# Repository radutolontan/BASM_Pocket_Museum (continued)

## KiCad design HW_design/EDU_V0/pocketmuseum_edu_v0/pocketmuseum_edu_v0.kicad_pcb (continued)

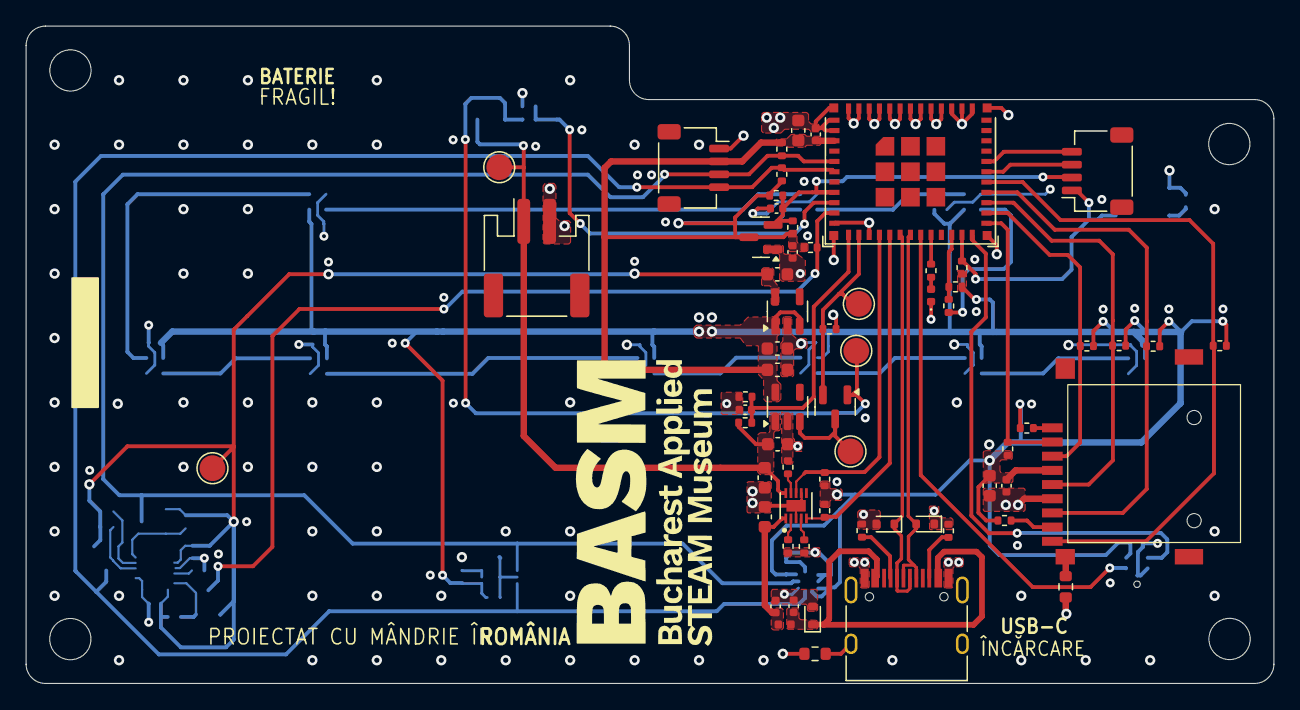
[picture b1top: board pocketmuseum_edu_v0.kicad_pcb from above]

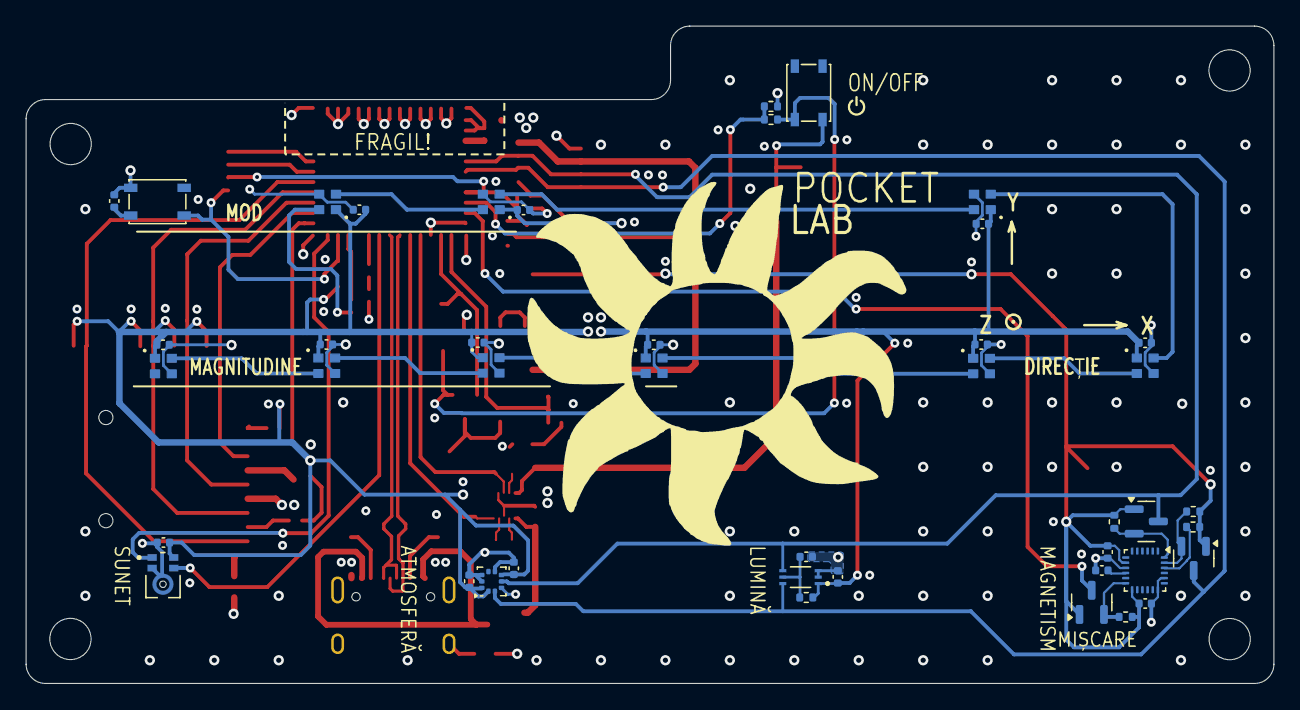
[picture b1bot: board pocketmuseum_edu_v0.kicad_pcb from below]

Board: 4 copper layers, 96.8 x 51.0 mm, 111 parts (43 on the bottom side), 56 nets.

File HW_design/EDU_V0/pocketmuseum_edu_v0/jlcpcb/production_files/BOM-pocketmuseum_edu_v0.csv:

Comment,Designator,Footprint,LCSC,Quantity
TF-015,J201,TF-015_SOFNG,C113206,1
1k,R308,R_0402_1005Metric,C11702,1
1u,"C101,C102,C105,C204,C301,C307,C401,C402,C403,C404,C405,C406,C407,C408,C409",C_0402_1005Metric,C14445,15
0u1,"C106,C202,C203,C207,C302,C303,C304,C305,C306,C308",C_0402_1005Metric,C1525,10
SM04B-SRSS-TB,"J205,J206",JST_SH_SM04B-SRSS-TB_1x04-1MP_P1.00mm_Horizontal,C160404,2
USB_C_Receptacle_USB2.0_16P,J101,USB_C_Receptacle_HRO_TYPE-C-31-M-12,C165948,1
10u,"C103,C104,C107,C108,C109,C110,C201,C206",C_0603_1608Metric,C1691,8
AP2112K-1.8,U104,SOT-23-5,C176944,1
BAT54C,D104,SOT-23,C181200,1
0R,"R114,R208",R_0603_1608Metric,C21189,2
LED,D208,LED_0402_1005Metric,C21260817,1
PTS810SJG250,"SW101,SW201",SW_SPST_PTS810,C221895,2
470R,R203,R_0402_1005Metric,C25117,1
100k,R110,R_0402_1005Metric,C25741,1
10k,"R105,R106,R107,R112,R113,R204,R205,R206,R207,R209,R210,R211,R212,R213,R214,R305",R_0402_1005Metric,C25744,16
1k2,"R103,R215",R_0402_1005Metric,C25862,2
3k3,R111,R_0402_1005Metric,C25890,1
5k1,"R101,R102,R201,R202,R301,R302,R303,R304",R_0402_1005Metric,C25905,8
6k8,R104,R_0402_1005Metric,C25917,1
178k,R109,R_0402_1005Metric,C26995,1
SK6805-EC20,"D401,D402,D403,D404,D405,D406,D407,D408,D409",SK68xx-EC20,C2890036,9
JST PH S2B,J102,JST_PH_S2B-PH-SM4-TB_1x02-1MP_P2.00mm_Horizontal,C295747,1
T3902,U304,MMIC,C3171752,1
61k9,R108,R_0402_1005Metric,C327331,1
APX803-29SAG,U102,SOT-23,C460551,1
AP2112K-3.3,U103,SOT-23-5,C51118,1
LESD5D5.0CT1G,"D101,D102,D103",D_SOD-523,C5199850,3
ICP20100,U302,ST_HLGA-10_2x2mm_P0.5mm_LayoutBorder3x2y,C5343527,1
ESP32-C6-MINI-1/U,U201,ESP32-C6-MINI-1,C5736265,1
ICM-20948,U301,InvenSense_QFN-24_3x3mm_P0.4mm,C726001,1
10n,L101,L_0402_1005Metric,C77103,1
BH1750FVI,U303,XDCR_BH1750FVI-TR,C78960,1
BQ24040,U101,QFN_10_BQ24040,C81080,1
BSS138,"Q301,Q302,Q303",SOT-23,C8490,3
TestPoint,TP105,TestPoint_Pad_D2.0mm,,1
TestPoint,TP101,TestPoint_Pad_D2.0mm,,1
TestPoint,TP104,TestPoint_Pad_D2.0mm,,1
TestPoint,TP102,TestPoint_Pad_D2.0mm,,1
TestPoint,TP103,TestPoint_Pad_D2.0mm,,1

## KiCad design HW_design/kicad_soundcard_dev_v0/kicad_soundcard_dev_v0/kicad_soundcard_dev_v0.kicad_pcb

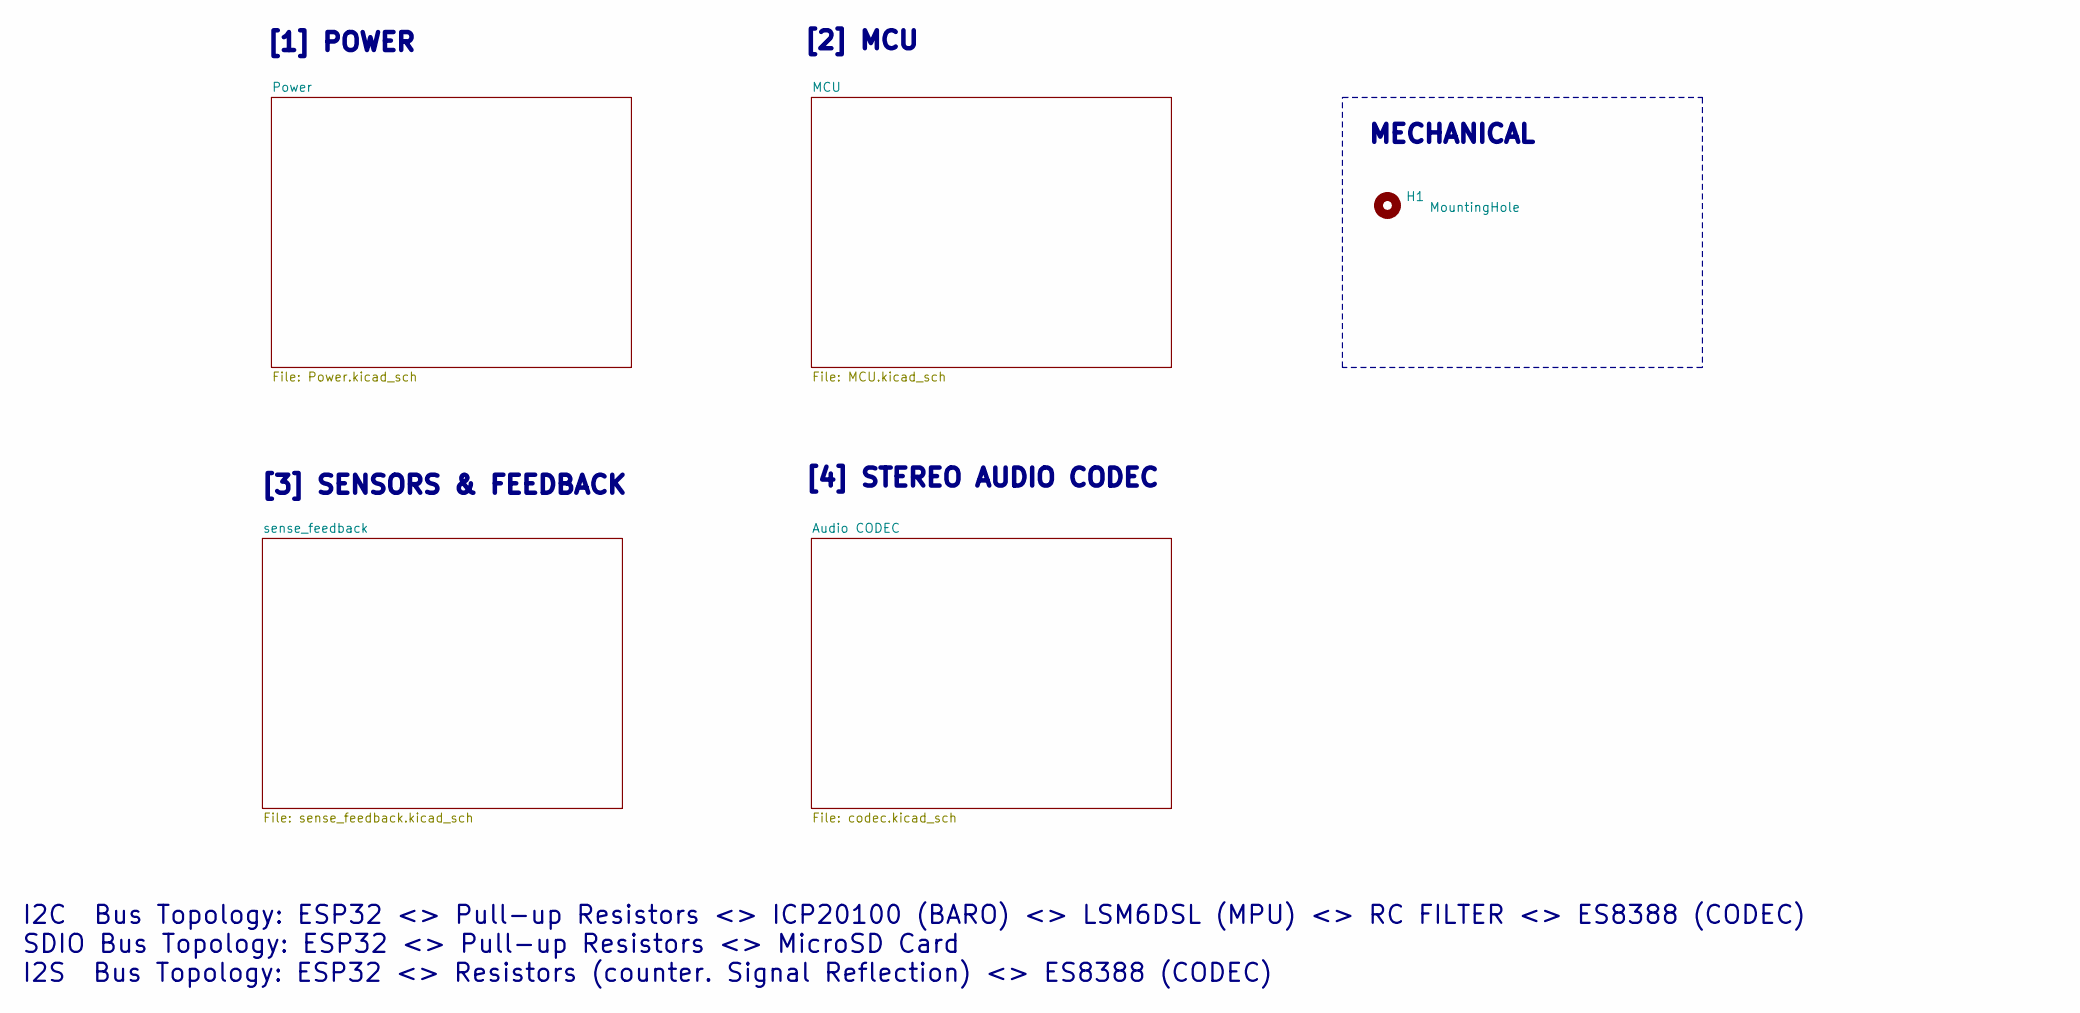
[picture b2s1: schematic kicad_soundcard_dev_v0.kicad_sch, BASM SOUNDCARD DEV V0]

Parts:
H1: MountingHole; MountingHole_3.5mm

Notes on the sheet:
[4] STEREO AUDIO CODEC
[1] POWER
I2C Bus Topology: ESP32 <> Pull-up Resistors <> ICP20100 (BARO) <> LSM6DSL (MPU) <> RC FILTER <> ES8388 (CODEC) SDIO Bus Topology: ESP32 <> Pull-up Resistors <> MicroSD Card I2S Bus Topology: ESP32 <> Resistors (counter. Signal Reflection) <> ES8388 (CODEC)
[2] MCU
[3] SENSORS & FEEDBACK
MECHANICAL

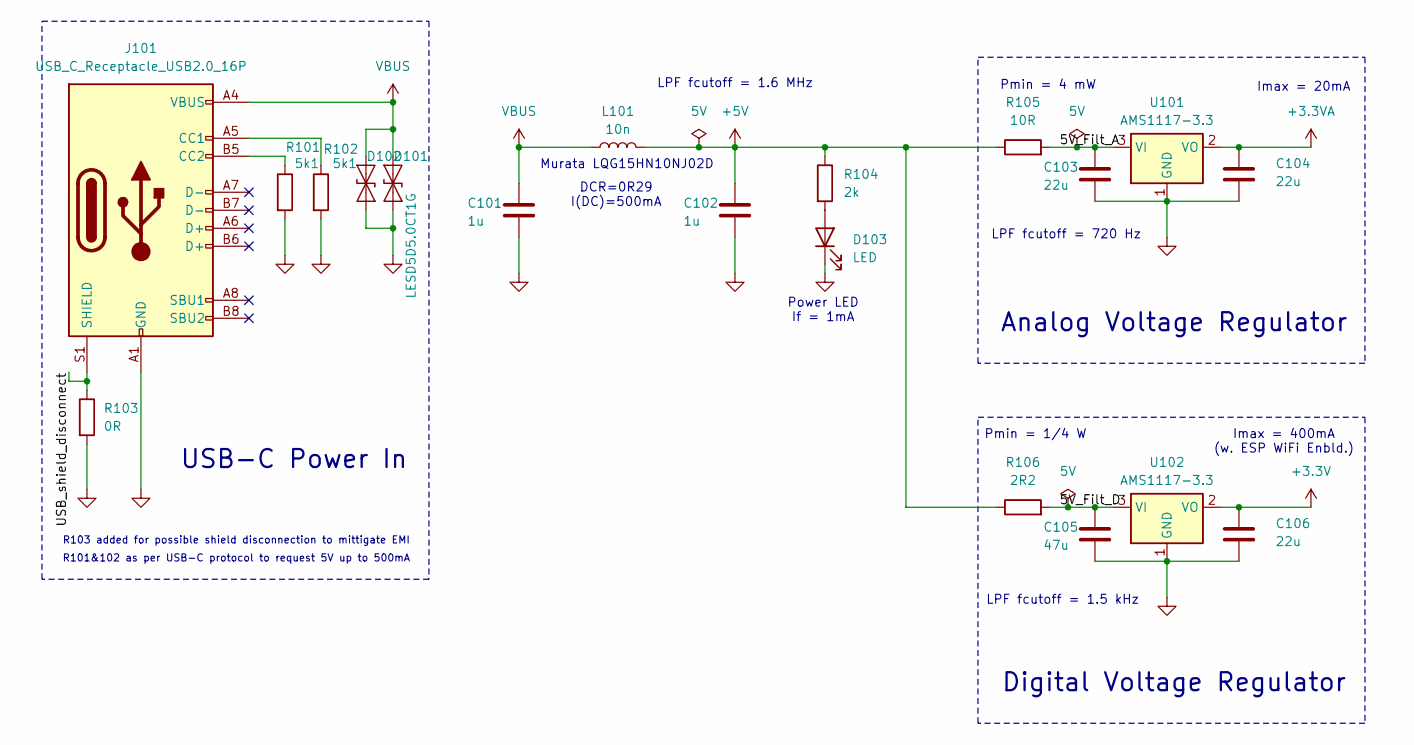
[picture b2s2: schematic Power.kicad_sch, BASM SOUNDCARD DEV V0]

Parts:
C101, C102: 1u; C_0402_1005Metric
C103, C104, C106: 22u; C_0603_1608Metric
C105: 47u; C_0603_1608Metric
D101, D102: LESD5D5.0CT1G; D_SOD-523
D103: LED; LED_0402_1005Metric
J101: USB_C_Receptacle_USB2.0_16P; USB_C_Receptacle_HRO_TYPE-C-31-M-12
L101: 10n; L_0402_1005Metric
R101, R102: 5k1; R_0402_1005Metric
R103: 0R; R_0603_1608Metric
R104: 2k; R_0402_1005Metric
R105: 10R; R_0603_1608Metric
R106: 2R2; R_1206_3216Metric
U101, U102: AMS1117-3.3; SOT-223-3_TabPin2

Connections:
+3.3V: C106.1, U102.2 (VO); also elsewhere on the board
+3.3VA: C104.1, U101.2 (VO); also elsewhere on the board
+5V: C102.1, L101.2, R104.1, R105.1, R106.1
/Power/5V_Filt_A: C103.1, R105.2, U101.3 (VI)
/Power/5V_Filt_D: C105.1, R106.2, U102.3 (VI)
/Power/USB_shield_disconnect: J101.S1 (SHIELD), R103.1
GND: C101.2, C102.2, C103.2, C104.2, C105.2, C106.2, D101.1 (A1), D102.1 (A1), D103.1 (K), J101.A1 (GND), J101.A12 (GND), J101.B1 (GND), J101.B12 (GND), R101.2, R102.2, R103.2, U101.1 (GND), U102.1 (GND); also elsewhere on the board
unnamed: D103.2 (A), R104.2
unnamed: J101.A5 (CC1), R102.1
unnamed: J101.B5 (CC2), R101.1
VBUS: C101.1, D101.2 (A2), D102.2 (A2), J101.A4 (VBUS), J101.A9 (VBUS), J101.B4 (VBUS), J101.B9 (VBUS), L101.1; also elsewhere on the board

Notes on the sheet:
Analog Voltage Regulator
Murata LQG15HN10NJ02D
Imax = 20mA
Pmin = 1/4 W
LPF fcutoff = 1.5 kHz
Pmin = 4 mW
DCR=0R29 I(DC)=500mA
USB-C Power In
Imax = 400mA (w. ESP WiFi Enbld.)
Power LED If = 1mA
Digital Voltage Regulator
LPF fcutoff = 1.6 MHz
R103 added for possible shield disconnection to mittigate EMI
R101&102 as per USB-C protocol to request 5V up to 500mA
LPF fcutoff = 720 Hz

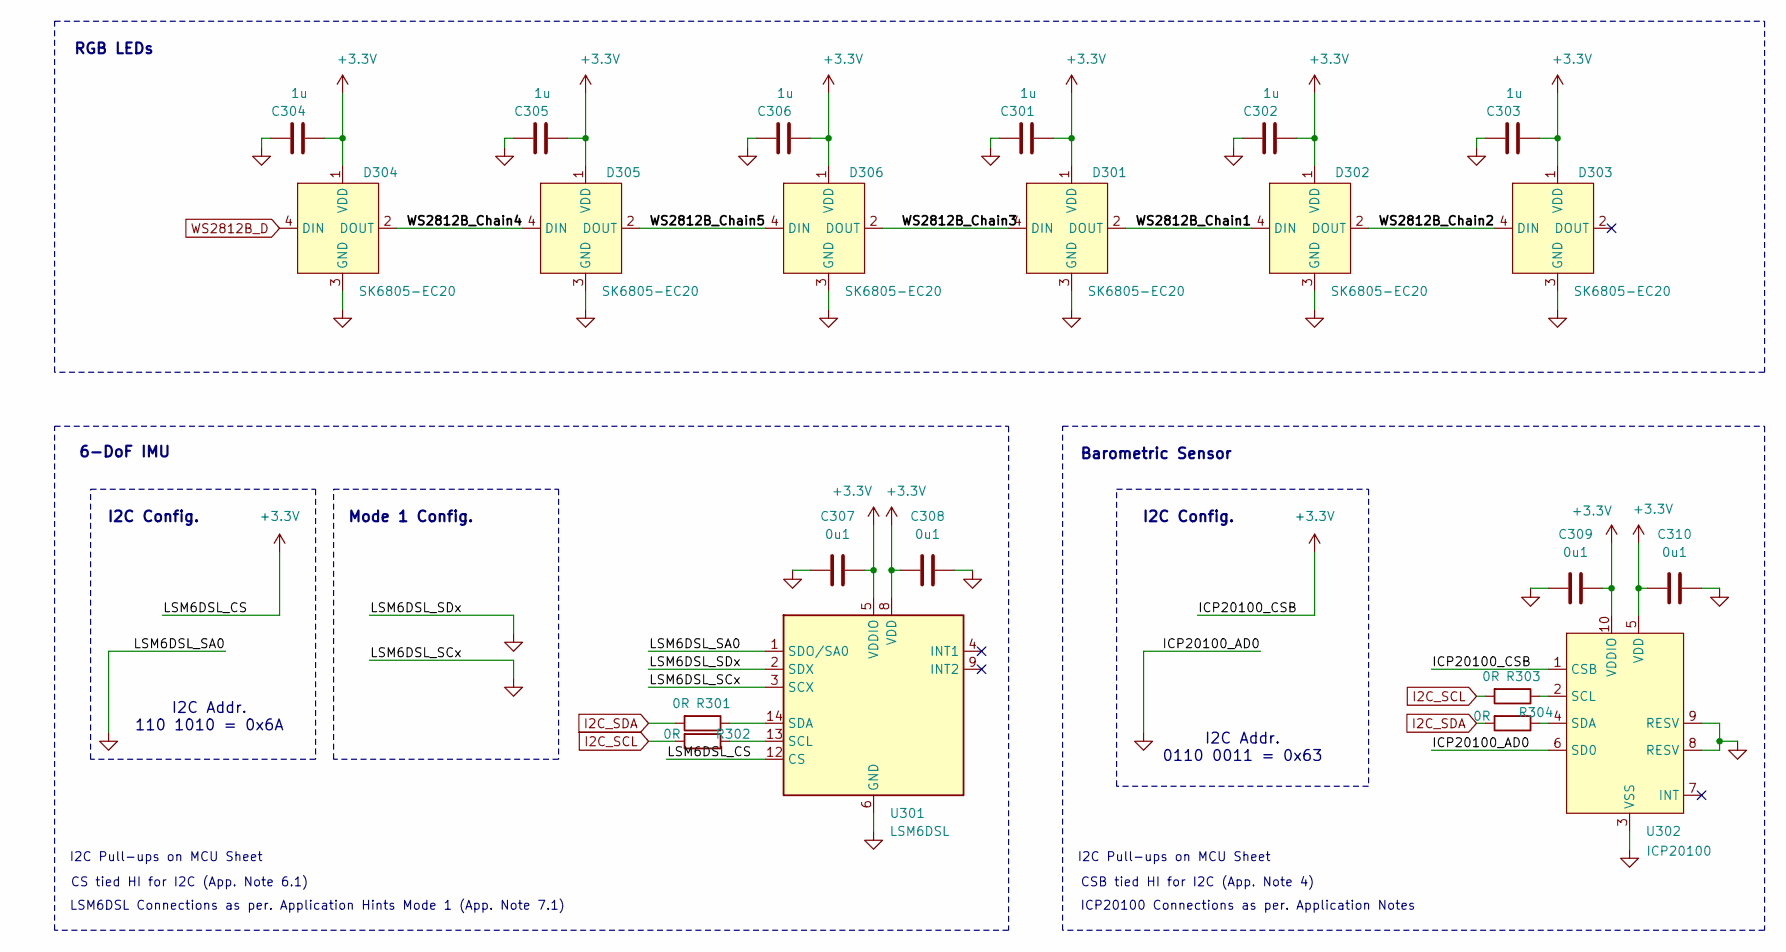
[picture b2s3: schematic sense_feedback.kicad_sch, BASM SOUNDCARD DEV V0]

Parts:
C301, C302, C303, C304, C305, C306: 1u; C_0402_1005Metric
C307, C308, C309, C310: 0u1; C_0402_1005Metric
D301, D302, D303, D304, D305, D306: SK6805-EC20; SK68xx-EC20
R301, R302, R303, R304: 0R; R_0603_1608Metric
U301: LSM6DSL; LGA-14_3x2.5mm_P0.5mm_LayoutBorder3x4y
U302: ICP20100; ST_HLGA-10_2x2mm_P0.5mm_LayoutBorder3x2y

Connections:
+3.3V: C301.2, C302.2, C303.2, C304.2, C305.2, C306.2, C307.1, C308.2, C309.1, C310.2, D301.1 (VDD), D302.1 (VDD), D303.1 (VDD), D304.1 (VDD), D305.1 (VDD), D306.1 (VDD), U301.5 (VDDIO), U301.8 (VDD), U301.12 (CS), U302.1 (CSB), U302.5 (VDD), U302.10 (VDDIO); also elsewhere on the board
/sense_feedback/WS2812B_Chain1: D301.2 (DOUT), D302.4 (DIN)
/sense_feedback/WS2812B_Chain2: D302.2 (DOUT), D303.4 (DIN)
/sense_feedback/WS2812B_Chain3: D301.4 (DIN), D306.2 (DOUT)
/sense_feedback/WS2812B_Chain4: D304.2 (DOUT), D305.4 (DIN)
/sense_feedback/WS2812B_Chain5: D305.2 (DOUT), D306.4 (DIN)
GND: C301.1, C302.1, C303.1, C304.1, C305.1, C306.1, C307.2, C308.1, C309.2, C310.1, D301.3 (GND), D302.3 (GND), D303.3 (GND), D304.3 (GND), D305.3 (GND), D306.3 (GND), U301.1 (SDO/SA0), U301.2 (SDX), U301.3 (SCX), U301.6 (GND), U301.7 (GND), U302.3 (VSS), U302.6 (SD0), U302.8 (RESV), U302.9 (RESV); also elsewhere on the board
I2C_SCL: R302.2, R303.2; also elsewhere on the board
I2C_SDA: R301.2, R304.2; also elsewhere on the board
unnamed: R302.1, U301.13 (SCL)
unnamed: R301.1, U301.14 (SDA)
unnamed: R303.1, U302.2 (SCL)
unnamed: R304.1, U302.4 (SDA)
WS2812B_D: D304.4 (DIN); also elsewhere on the board

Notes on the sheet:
CS tied HI for I2C (App. Note 6.1)
I2C Config.
I2C Addr. 0110 0011 = 0x63
CSB tied HI for I2C (App. Note 4)
ICP20100 Connections as per. Application Notes
Barometric Sensor
I2C Pull-ups on MCU Sheet
Mode 1 Config.
RGB LEDs
I2C Addr. 110 1010 = 0x6A
6-DoF IMU
LSM6DSL Connections as per. Application Hints Mode 1 (App. Note 7.1)

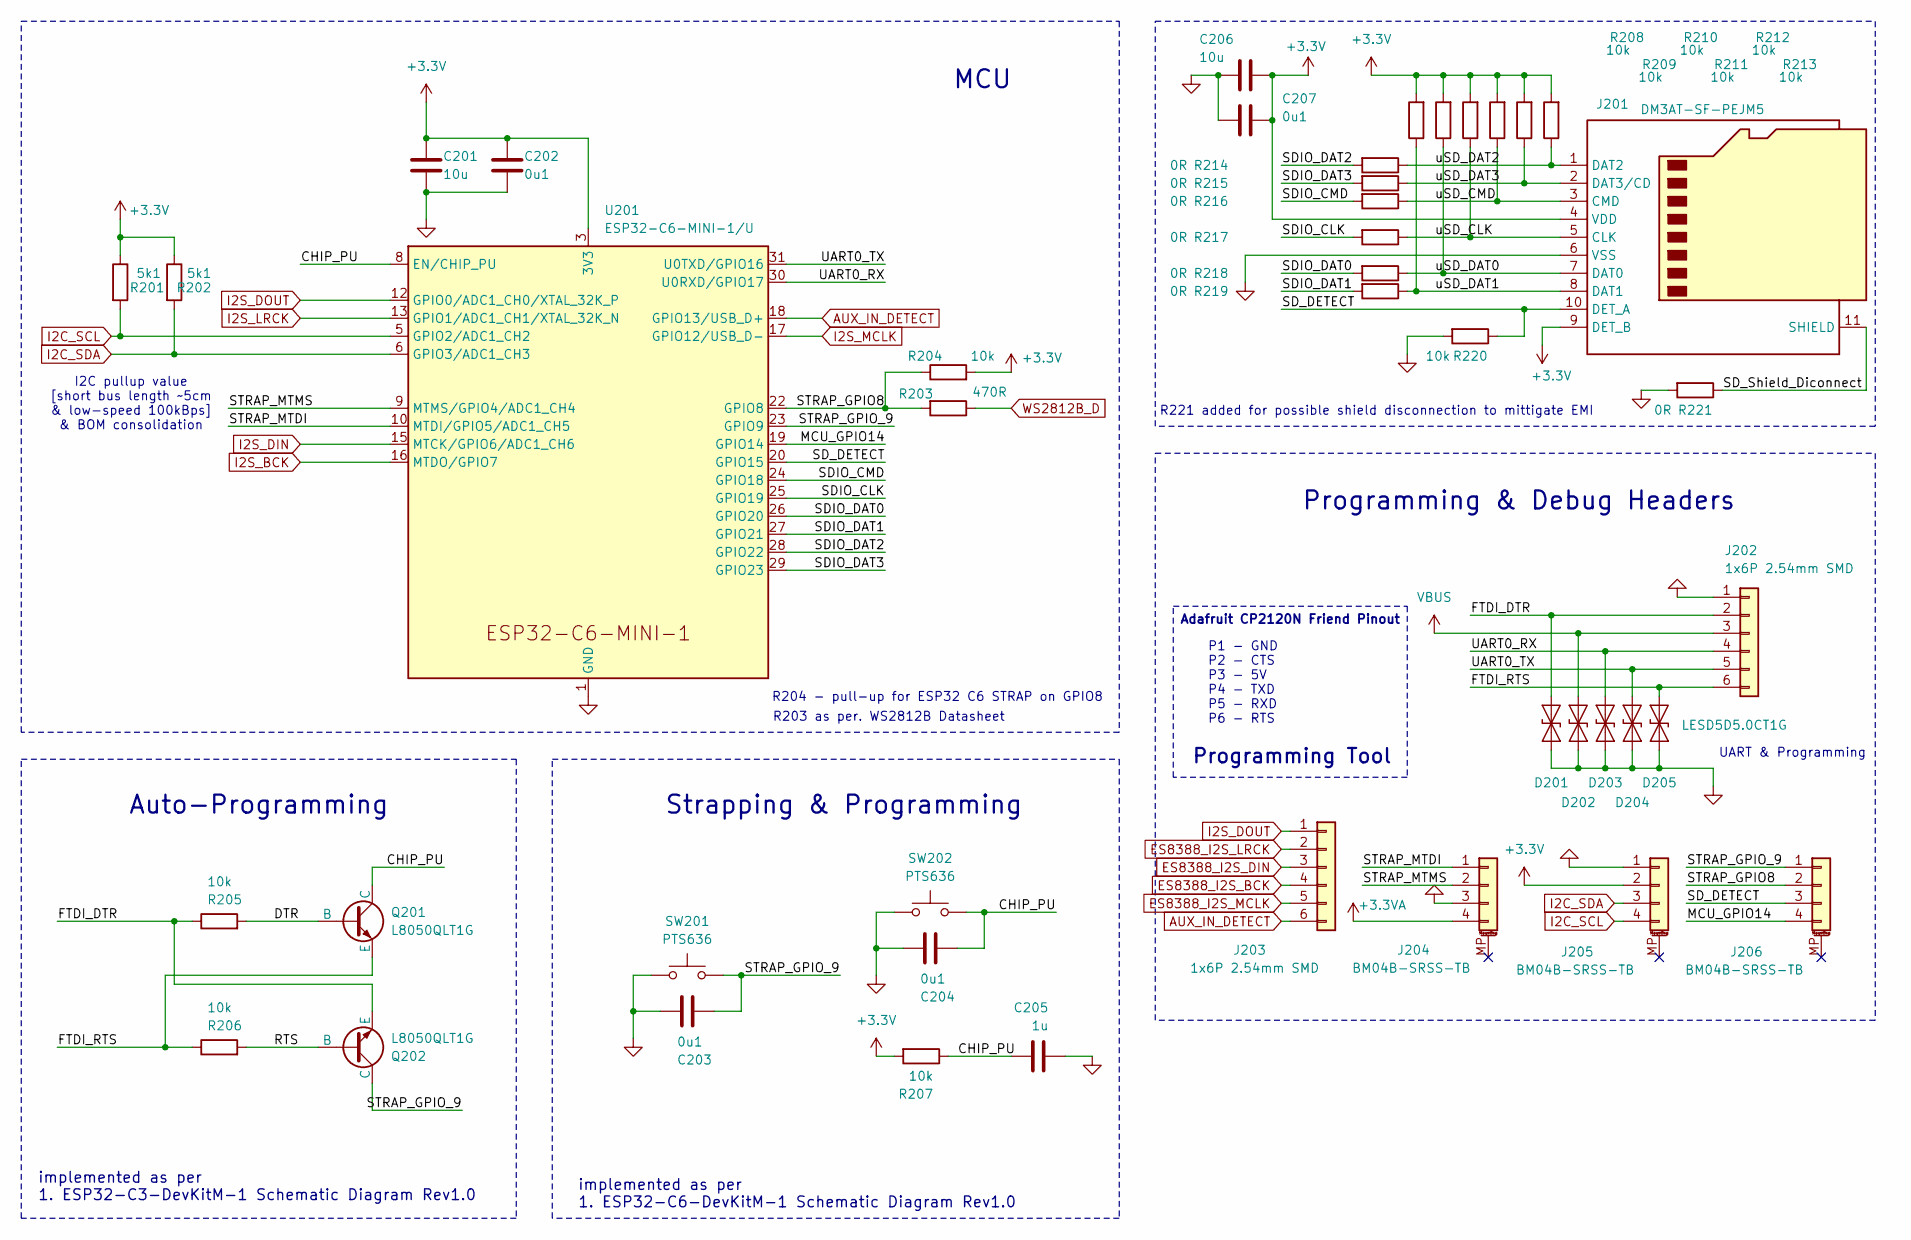
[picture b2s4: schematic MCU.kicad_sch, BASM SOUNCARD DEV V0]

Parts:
C201, C206: 10u; C_0603_1608Metric; Manufacturer P/N CL10A106MQ8NNNC
C202, C203, C204, C207: 0u1; C_0402_1005Metric; Manufacturer P/N CL05B104KO5NNNC
C205: 1u; C_0402_1005Metric; Manufacturer P/N CL05A105KP5NNNC
D201, D202, D203, D204, D205: LESD5D5.0CT1G; D_SOD-523; Manufacturer P/N LESD5D5.0CT1G
J201: DM3AT-SF-PEJM5; microSD_HC_Hirose_DM3AT-SF-PEJM5; Manufacturer P/N DM3AT-SF-PEJM5
J202, J203: 1x6P 2.54mm SMD; PinHeader_1x06_P2.54mm_Vertical_SMD_Pin1Right; Manufacturer P/N X6511WVS-06H-C60D48R1
J204, J205, J206: BM04B-SRSS-TB; JST_SH_BM04B-SRSS-TB_1x04-1MP_P1.00mm_Vertical; Manufacturer P/N BM04B-SRSS-TB(LF)(SN)
Q201, Q202: L8050QLT1G; SOT-23; Manufacturer P/N L8050QLT1G
R201, R202: 5k1; R_0402_1005Metric; Manufacturer P/N 0402WGF5101TCE
R203: 470R; R_0402_1005Metric; Manufacturer P/N 0402WGF4700TCE
R204, R205, R206, R207, R208, R209, R210, R211, R212, R213, R220: 10k; R_0402_1005Metric; Manufacturer P/N 0402WGF1002TCE
R214, R215, R216, R217, R218, R219, R221: 0R; R_0603_1608Metric; Manufacturer P/N 0603WAJ0000T5E
SW201, SW202: PTS636; SW_Tactile_SPST_NO_Straight_CK_PTS636Sx25SMTRLFS; Manufacturer P/N PTS636SK25SMTRLFS
U201: ESP32-C6-MINI-1/U; ESP32-C6-MINI-1; Manufacturer P/N ESP32-C6-MINI-1-N4

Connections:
+3.3V: C201.1, C202.1, C206.1, C207.1, J201.4 (VDD), J201.9 (DET_B), J205.2, R201.1, R202.1, R204.2, R207.2, R208.2, R209.2, R210.2, R211.2, R212.2, R213.2, U201.3 (3V3); also elsewhere on the board
+3.3VA: J204.4; also elsewhere on the board
/MCU/CHIP_PU: C204.1, C205.1, Q201.1 (C), R207.1, SW202.2, U201.8 (EN/CHIP_PU)
/MCU/DTR: Q201.2 (B), R205.2
/MCU/FTDI_DTR: D201.2 (A2), J202.2, Q202.3 (E), R205.1
/MCU/FTDI_RTS: D205.2 (A2), J202.6, Q201.3 (E), R206.1
/MCU/MCU_GPIO14: J206.4, U201.19 (GPIO14)
/MCU/RTS: Q202.2 (B), R206.2
/MCU/SDIO_CLK: R217.2, U201.25 (GPIO19)
/MCU/SDIO_CMD: R216.2, U201.24 (GPIO18)
/MCU/SDIO_DAT0: R218.2, U201.26 (GPIO20)
/MCU/SDIO_DAT1: R219.2, U201.27 (GPIO21)
/MCU/SDIO_DAT2: R214.2, U201.28 (GPIO22)
/MCU/SDIO_DAT3: R215.2, U201.29 (GPIO23)
/MCU/SD_DETECT: J201.10 (DET_A), J206.3, R220.1, U201.20 (GPIO15)
/MCU/SD_Shield_Diconnect: J201.11 (SHIELD), R221.1
/MCU/STRAP_GPIO8: J206.2, R203.2, R204.1, U201.22 (GPIO8)
/MCU/STRAP_GPIO_9: C203.1, J206.1, Q202.1 (C), SW201.2, U201.23 (GPIO9)
/MCU/STRAP_MTDI: J204.1, U201.10 (MTDI/GPIO5/ADC1_CH5)
/MCU/STRAP_MTMS: J204.2, U201.9 (MTMS/GPIO4/ADC1_CH4)
/MCU/UART0_RX: D203.2 (A2), J202.4, U201.30 (U0RXD/GPIO17)
/MCU/UART0_TX: D204.2 (A2), J202.5, U201.31 (U0TXD/GPIO16)
/MCU/uSD_CLK: J201.5 (CLK), R210.1, R217.1
/MCU/uSD_CMD: J201.3 (CMD), R211.1, R216.1
/MCU/uSD_DAT0: J201.7 (DAT0), R209.1, R218.1
/MCU/uSD_DAT1: J201.8 (DAT1), R208.1, R219.1
/MCU/uSD_DAT2: J201.1 (DAT2), R213.1, R214.1
/MCU/uSD_DAT3: J201.2 (DAT3/CD), R212.1, R215.1
AUX_IN_DETECT: J203.6, U201.18 (GPIO13/USB_D+); also elsewhere on the board
ES8388_I2S_BCK: J203.4; also elsewhere on the board
ES8388_I2S_DIN: J203.3; also elsewhere on the board
ES8388_I2S_LRCK: J203.2; also elsewhere on the board
ES8388_I2S_MCLK: J203.5; also elsewhere on the board
GND: C201.2, C202.2, C203.2, C204.2, C205.2, C206.2, C207.2, D201.1 (A1), D202.1 (A1), D203.1 (A1), D204.1 (A1), D205.1 (A1), J201.6 (VSS), J202.1, J204.3, J205.1, R220.2, R221.2, SW201.1, SW202.1, U201.1 (GND), U201.2 (GND), U201.11 (GND), U201.14 (GND), U201.36 (GND), U201.37 (GND), U201.38 (GND), U201.39 (GND), U201.40 (GND), U201.41 (GND), U201.42 (GND), U201.43 (GND), U201.44 (GND), U201.45 (GND), U201.46 (GND), U201.47 (GND), U201.48 (GND), U201.49 (GND), U201.50 (GND), U201.51 (GND), U201.52 (GND), U201.53 (GND); also elsewhere on the board
I2C_SCL: J205.4, R201.2, U201.5 (GPIO2/ADC1_CH2); also elsewhere on the board
I2C_SDA: J205.3, R202.2, U201.6 (GPIO3/ADC1_CH3); also elsewhere on the board
I2S_BCK: U201.16 (MTDO/GPIO7); also elsewhere on the board
I2S_DIN: U201.15 (MTCK/GPIO6/ADC1_CH6); also elsewhere on the board
I2S_DOUT: J203.1, U201.12 (GPIO0/ADC1_CH0/XTAL_32K_P); also elsewhere on the board
I2S_LRCK: U201.13 (GPIO1/ADC1_CH1/XTAL_32K_N); also elsewhere on the board
I2S_MCLK: U201.17 (GPIO12/USB_D-); also elsewhere on the board
VBUS: D202.2 (A2), J202.3; also elsewhere on the board
WS2812B_D: R203.1; also elsewhere on the board

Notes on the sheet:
R203 as per. WS2812B Datasheet
Adafruit CP2120N Friend Pinout
Programming & Debug Headers
R221 added for possible shield disconnection to mittigate EMI
implemented as per 1. ESP32-C6-DevKitM-1 Schematic Diagram Rev1.0
UART & Programming
Strapping & Programming
R204 - pull-up for ESP32 C6 STRAP on GPIO8
P1 - GND P2 - CTS P3 - 5V P4 - TXD P5 - RXD P6 - RTS
I2C pullup value [short bus length ~5cm & low-speed 100kBps] & BOM consolidation
MCU
Programming Tool
implemented as per 1. ESP32-C3-DevKitM-1 Schematic Diagram Rev1.0
Auto-Programming

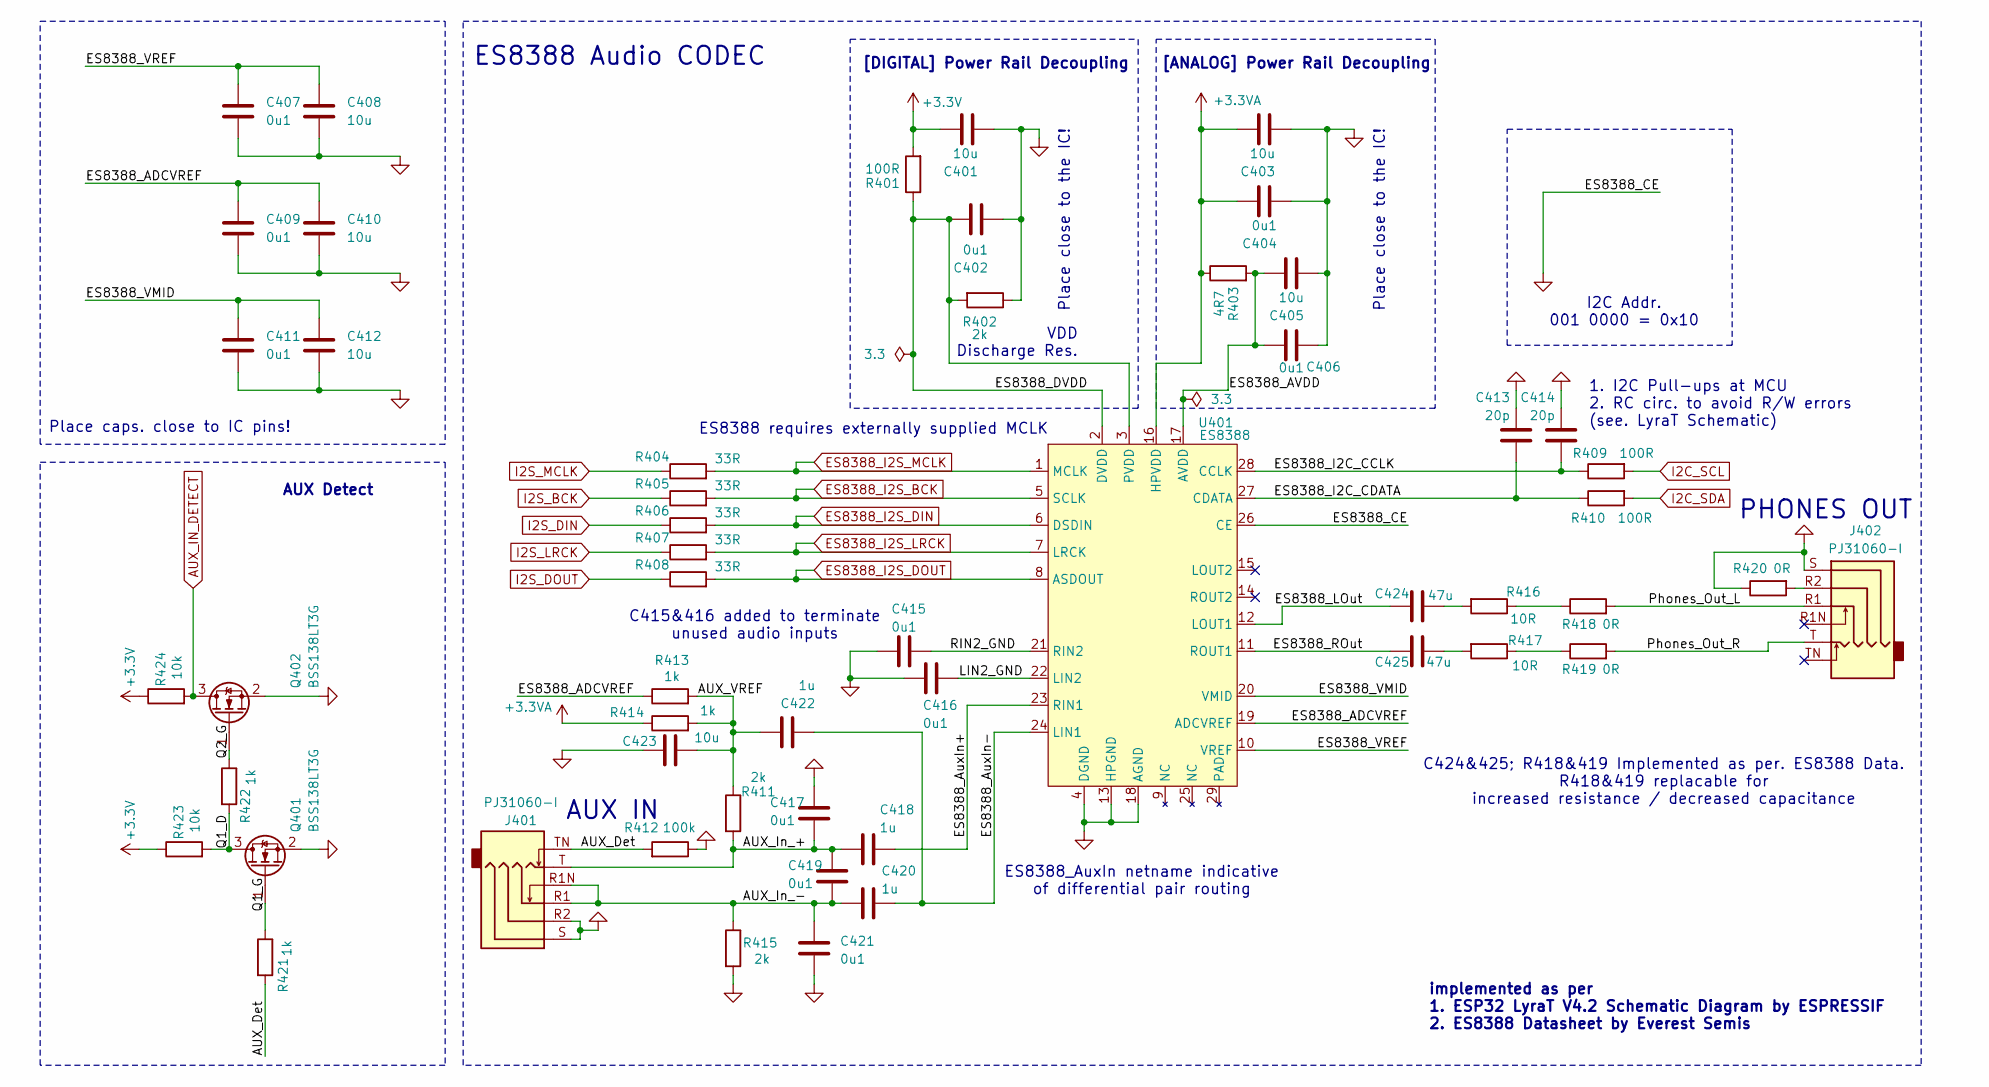
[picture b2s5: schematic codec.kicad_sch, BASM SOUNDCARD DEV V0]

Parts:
C401, C403, C405, C408, C410, C412, C423: 10u; C_0603_1608Metric
C402, C404, C406, C407, C409, C411, C415, C416, C417, C419, C421: 0u1; C_0402_1005Metric
C413, C414: 20p; C_0402_1005Metric
C418, C420, C422: 1u; C_0402_1005Metric
C424, C425: 47u; C_0603_1608Metric
J401, J402: PJ31060-I; Jack_3.5mm_PJ31060-I_Horizontal
Q401, Q402: BSS138LT3G; SOT-23
R401, R409, R410: 100R; R_0402_1005Metric
R402, R411, R415: 2k; R_0402_1005Metric
R403: 4R7; R_0402_1005Metric
R404, R405, R406, R407, R408: 33R; R_0402_1005Metric
R412: 100k; R_0402_1005Metric
R413, R414, R421, R422: 1k; R_0402_1005Metric
R416, R417: 10R; R_0603_1608Metric
R418, R419, R420: 0R; R_0603_1608Metric
R423, R424: 10k; R_0402_1005Metric
U401: ES8388; QFN-28-1EP_4x4mm_P0.4mm_EP2.6x2.6mm

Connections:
+3.3V: C401.1, R401.2, R423.1, R424.1; also elsewhere on the board
+3.3VA: C403.1, C404.1, R403.1, R414.1, U401.16 (HPVDD); also elsewhere on the board
/Audio CODEC/AUX_Det: J401.TN, R412.2, R421.2
/Audio CODEC/AUX_In_+: C417.2, C418.2, C419.1, J401.T, R411.2
/Audio CODEC/AUX_In_-: C419.2, C420.2, C421.1, J401.R1, J401.R1N, R415.1
/Audio CODEC/AUX_VREF: C422.1, C423.1, R411.1, R413.2, R414.2
/Audio CODEC/ES8388_ADCVREF: C409.1, C410.1, R413.1, U401.19 (ADCVREF)
/Audio CODEC/ES8388_AVDD: C405.1, C406.1, R403.2, U401.17 (AVDD)
/Audio CODEC/ES8388_AuxIn+: C418.1, U401.23 (RIN1)
/Audio CODEC/ES8388_AuxIn-: C420.1, C422.2, U401.24 (LIN1)
/Audio CODEC/ES8388_DVDD: C402.1, R401.1, R402.2, U401.2 (DVDD), U401.3 (PVDD)
/Audio CODEC/ES8388_I2C_CCLK: C414.2, R409.1, U401.28 (CCLK)
/Audio CODEC/ES8388_I2C_CDATA: C413.2, R410.1, U401.27 (CDATA)
/Audio CODEC/ES8388_LOut: C424.2, U401.12 (LOUT1)
/Audio CODEC/ES8388_ROut: C425.2, U401.11 (ROUT1)
/Audio CODEC/ES8388_VMID: C411.1, C412.1, U401.20 (VMID)
/Audio CODEC/ES8388_VREF: C407.1, C408.1, U401.10 (VREF)
/Audio CODEC/LIN2_GND: C416.1, U401.22 (LIN2)
/Audio CODEC/Phones_Out_L: J402.R1, R418.2
/Audio CODEC/Phones_Out_R: J402.T, R419.2
/Audio CODEC/Q1_D: Q401.3 (D), R422.2, R423.2
/Audio CODEC/Q1_G: Q401.1 (G), R421.1
/Audio CODEC/Q2_G: Q402.1 (G), R422.1
/Audio CODEC/RIN2_GND: C415.1, U401.21 (RIN2)
AUX_IN_DETECT: Q402.3 (D), R424.2; also elsewhere on the board
ES8388_I2S_BCK: R405.2, U401.5 (SCLK); also elsewhere on the board
ES8388_I2S_DIN: R406.2, U401.6 (DSDIN); also elsewhere on the board
ES8388_I2S_DOUT: R408.2, U401.8 (ASDOUT)
ES8388_I2S_LRCK: R407.2, U401.7 (LRCK); also elsewhere on the board
ES8388_I2S_MCLK: R404.2, U401.1 (MCLK); also elsewhere on the board
GND: C401.2, C402.2, C403.2, C404.2, C405.2, C406.2, C407.2, C408.2, C409.2, C410.2, C411.2, C412.2, C413.1, C414.1, C415.2, C416.2, C417.1, C421.2, C423.2, J401.R2, J401.S, J402.S, Q401.2 (S), Q402.2 (S), R402.1, R412.1, R415.2, R420.1, U401.4 (DGND), U401.13 (HPGND), U401.18 (AGND), U401.26 (CE); also elsewhere on the board
I2C_SCL: R409.2; also elsewhere on the board
I2C_SDA: R410.2; also elsewhere on the board
I2S_BCK: R405.1; also elsewhere on the board
I2S_DIN: R406.1; also elsewhere on the board
I2S_DOUT: R408.1; also elsewhere on the board
I2S_LRCK: R407.1; also elsewhere on the board
I2S_MCLK: R404.1; also elsewhere on the board
unnamed: C424.1, R416.2
unnamed: C425.1, R417.2
unnamed: J402.R2, R420.2
unnamed: R416.1, R418.1
unnamed: R417.1, R419.1

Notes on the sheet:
1. I2C Pull-ups at MCU 2. RC circ. to avoid R/W errors (see. LyraT Schematic)
ES8388 Audio CODEC
ES8388 requires externally supplied MCLK
Place caps. close to IC pins!
Place close to the IC!
ES8388_AuxIn netname indicative of differential pair routing
[ANALOG] Power Rail Decoupling
[DIGITAL] Power Rail Decoupling
PHONES OUT
AUX IN
C415&416 added to terminate unused audio inputs
implemented as per 1. ESP32 LyraT V4.2 Schematic Diagram by ESPRESSIF 2. ES8388 Datasheet by Everest Semis
AUX Detect
VDD Discharge Res.
C424&425; R418&419 Implemented as per. ES8388 Data. R418&419 replacable for increased resistance / decreased capacitance
I2C Addr. 001 0000 = 0x10

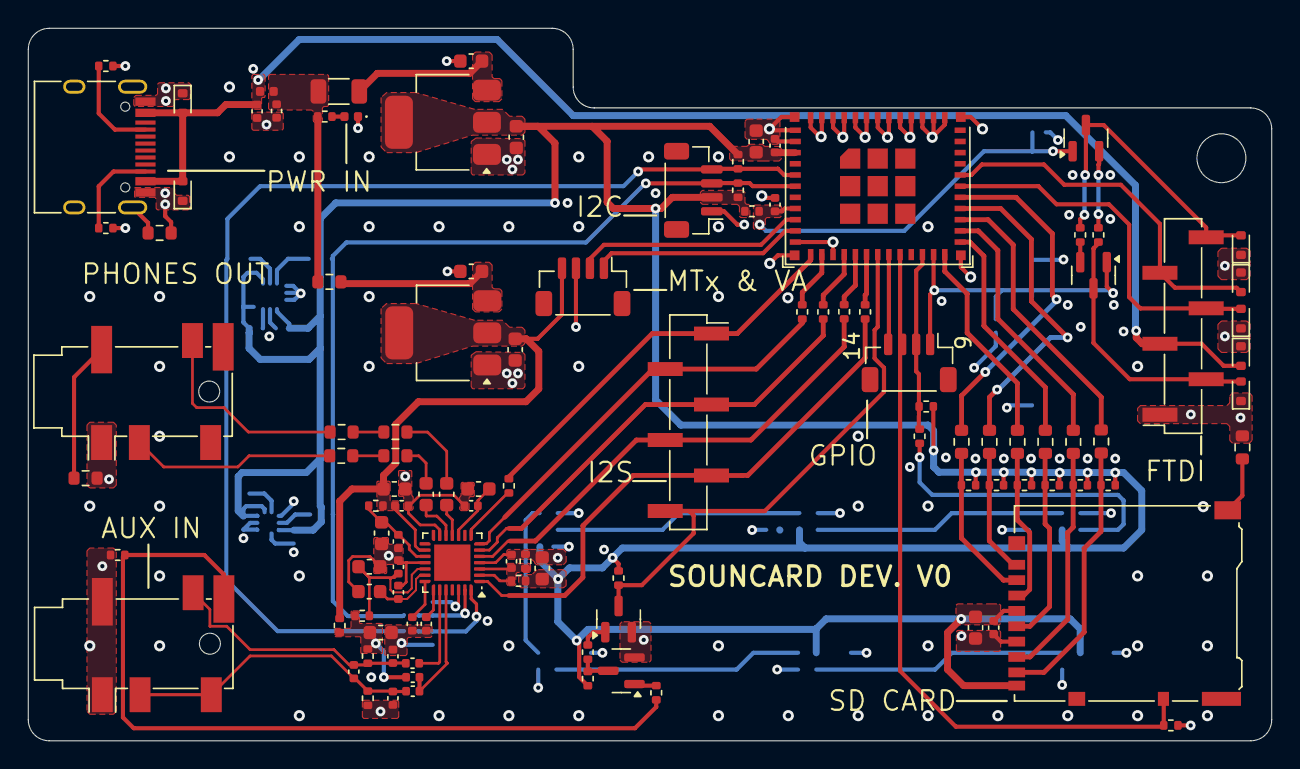
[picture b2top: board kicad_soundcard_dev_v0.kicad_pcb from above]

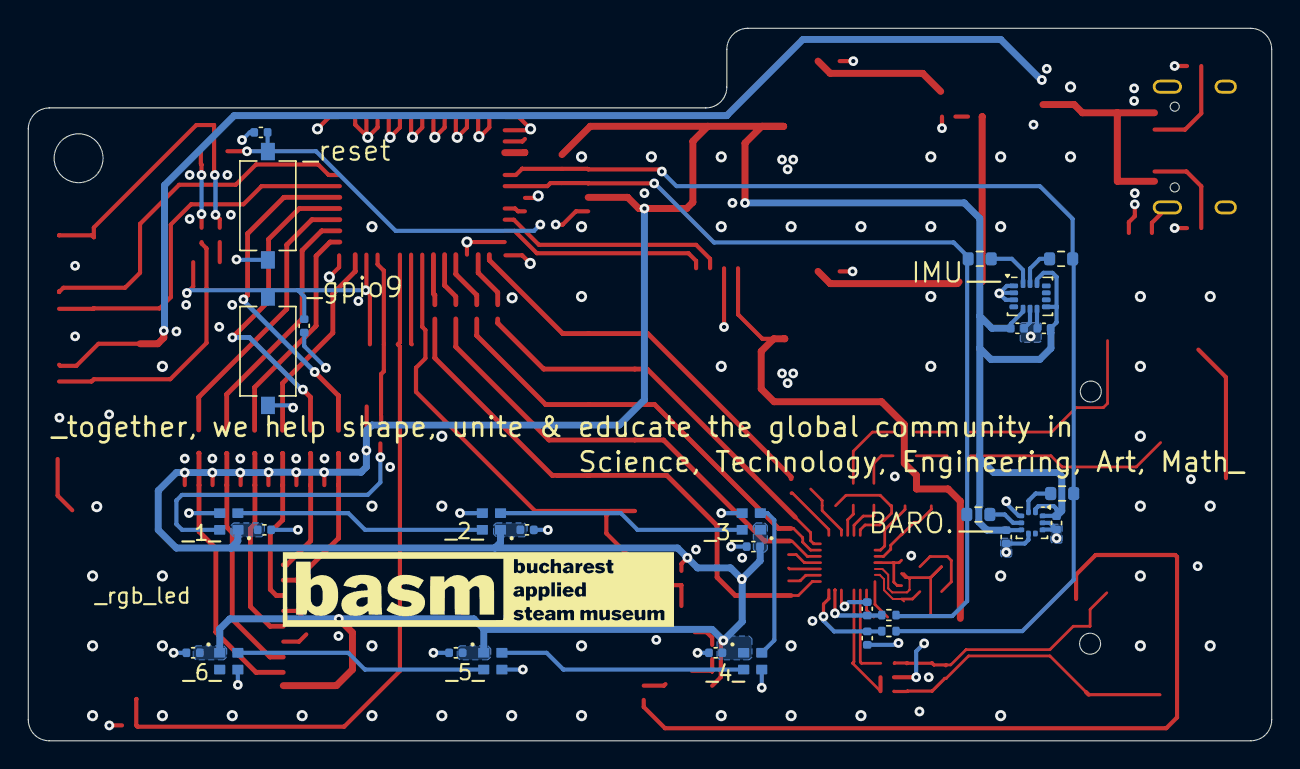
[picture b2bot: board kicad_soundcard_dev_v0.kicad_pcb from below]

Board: 4 copper layers, 89.0 x 51.0 mm, 140 parts (30 on the bottom side), 87 nets.
